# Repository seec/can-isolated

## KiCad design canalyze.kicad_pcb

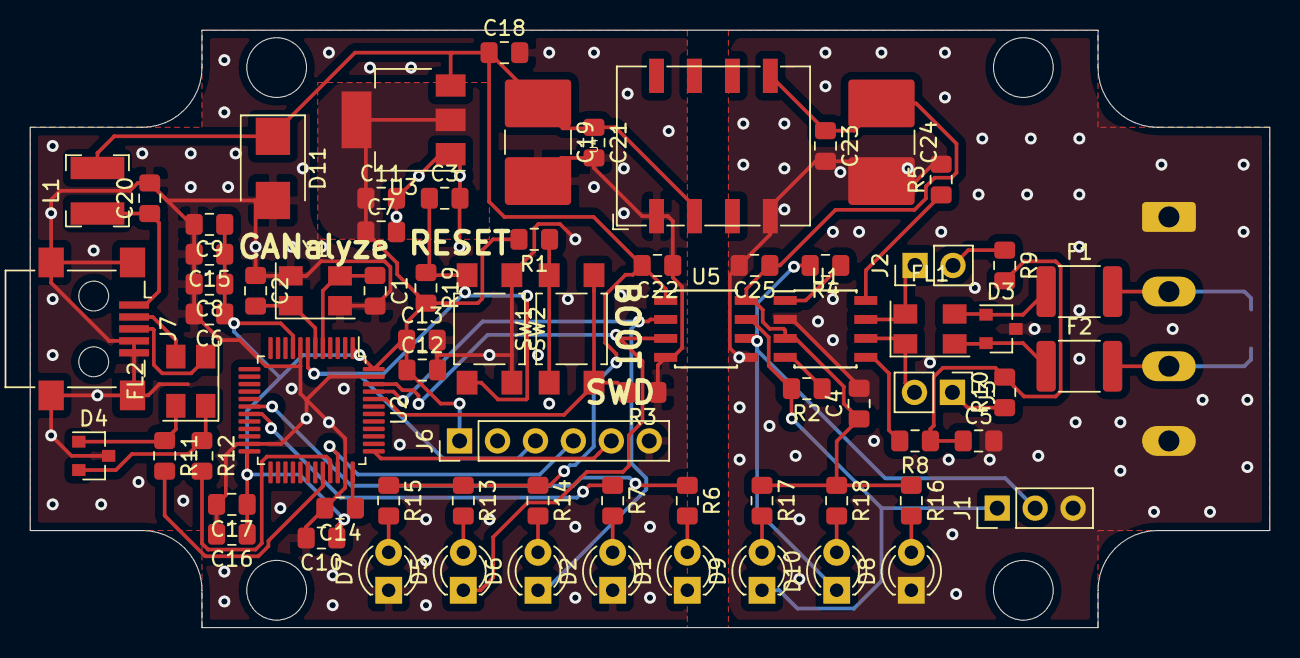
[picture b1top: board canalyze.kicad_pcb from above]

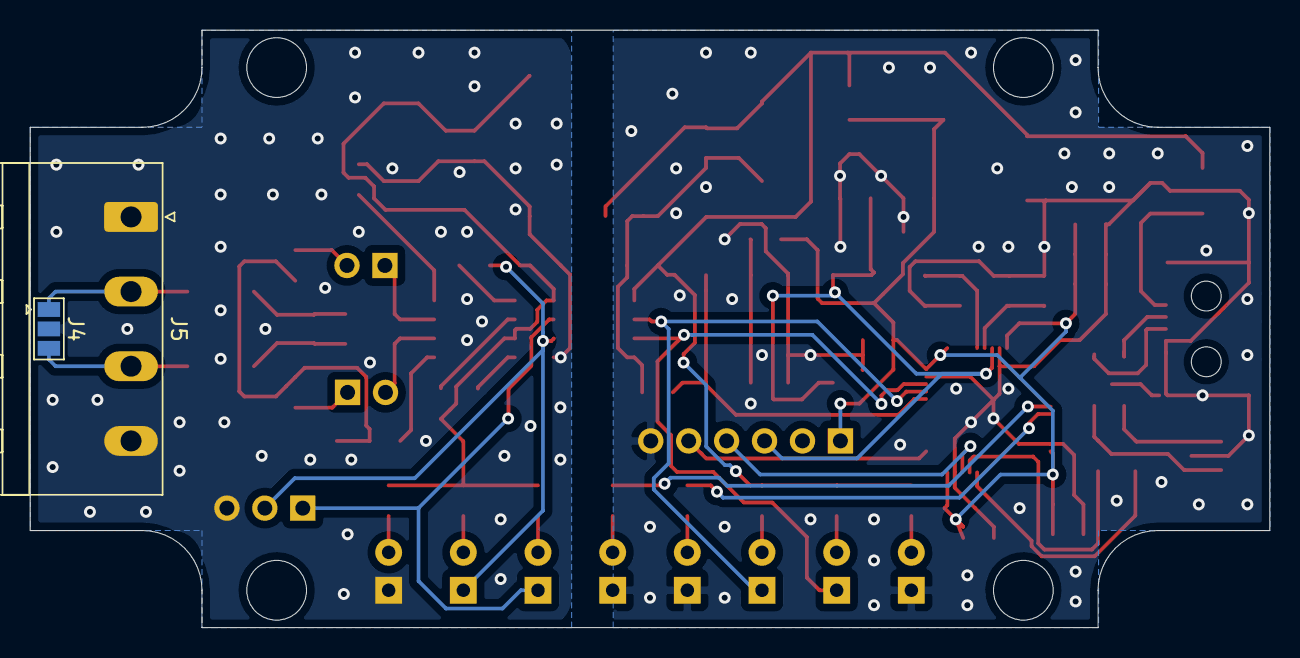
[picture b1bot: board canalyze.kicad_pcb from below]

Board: 2 copper layers, 83.0 x 40.0 mm, 75 parts (2 on the bottom side), 46 nets.

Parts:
C1, C2: 15p; C_0805_2012Metric_Pad1.15x1.40mm_HandSolder
C3, C6, C8, C9, C11, C12, C13: 0.1u; C_0805_2012Metric_Pad1.15x1.40mm_HandSolder
C4, C22, C25: 0.1U; C_0805_2012Metric_Pad1.15x1.40mm_HandSolder
C5: 10n; C_0805_2012Metric_Pad1.15x1.40mm_HandSolder
C7, C10, C14: 4.7u; C_0805_2012Metric_Pad1.15x1.40mm_HandSolder
C15: 0.01u; C_0805_2012Metric_Pad1.15x1.40mm_HandSolder
C16: 1u; C_0805_2012Metric_Pad1.15x1.40mm_HandSolder
C17, C18: 1U; C_0805_2012Metric_Pad1.15x1.40mm_HandSolder
C19, C24: CP; C_2816_7142Metric_Pad3.20x4.45mm_HandSolder
C20: 0.01U; C_0805_2012Metric_Pad1.15x1.40mm_HandSolder
C21, C23: C; C_0805_2012Metric_Pad1.15x1.40mm_HandSolder
D1: LED_GREEN; LED_D3.0mm
D2: LED_RED; LED_D3.0mm
D3, D4: PESD2CAN; SOT-23
D5, D6, D7, D8, D9, D10: LED; LED_D3.0mm
D11: 1.5KE6.5A; D_SMB
F1, F2: Polyfuse; Fuse_1812_4532Metric_Pad1.30x3.40mm_HandSolder
FL1, FL2: EMI_Filter_LL; Crystal_SMD_5032-4Pin_5.0x3.2mm
J1: Conn_01x03; PinHeader_1x03_P2.54mm_Vertical
J2, J3: Conn_01x02_Male; PinHeader_1x02_P2.54mm_Vertical
J4: GS3; SolderJumper-3_P1.3mm_Open_Pad1.0x1.5mm
J5: Conn_01x04_Male; PhoenixContact_MSTBA_2,5_4-G_1x04_P5.00mm_Horizontal
J6: Conn_01x06; PinHeader_1x06_P2.54mm_Vertical
J7: USB_B; USB_Mini-B_Lumberg_2486_01_Horizontal
L1: Ferrite_Bead; L_Bourns-SRN4018
R1: 510; R_0805_2012Metric_Pad1.15x1.40mm_HandSolder
R2, R4, R8: 300R; R_0805_2012Metric_Pad1.15x1.40mm_HandSolder
R3: 10k; R_0805_2012Metric_Pad1.15x1.40mm_HandSolder
R5: 2.2K; R_0805_2012Metric_Pad1.15x1.40mm_HandSolder
R6, R7: 120; R_0805_2012Metric_Pad1.15x1.40mm_HandSolder
R9, R10: 60R; R_0805_2012Metric_Pad1.15x1.40mm_HandSolder
R11, R12: 100R; R_0805_2012Metric_Pad1.15x1.40mm_HandSolder
R13, R14, R15, R16, R17, R18: 1K; R_0805_2012Metric_Pad1.15x1.40mm_HandSolder
R19: 100k; R_0805_2012Metric_Pad1.15x1.40mm_HandSolder
SW1, SW2: SW_PUSH; SW_SPST_TL3305A
U1: MCP2561-H/SN; SOIC-8_3.9x4.9mm_P1.27mm
U2: STM32F042C6Tx; LQFP-48_7x7mm_P0.5mm
U3: NCP1117-3.3_SOT223; SOT-223-3_TabPin2
U4: AM1L-N-Z
U5: ISO7321C; SOIC-8_3.9x4.9mm_P1.27mm
Y1: 16M; Crystal_SMD_5032-4Pin_5.0x3.2mm

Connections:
+3V3: C6.1, C7.1, C8.1, C9.1, C10.1, C11.1, C12.1, C13.1, C14.1, C15.1, C16.1, C17.1, J6.1, R1.2, R19.2, U2.1, U2.9, U2.24, U2.36, U2.48, U3.2
+5V: C18.1, C19.1, C21.1, C22.2, D11.1, L1.1, R13.1, R14.1, R15.1, U3.3, U4.2, U5.1
+5V1: C4.1, C23.1, C24.1, C25.1, R16.1, R17.1, R18.1, U1.3, U4.5, U5.8
/H: F1.2, J4.1, J5.2
/L: F2.2, J4.3, J5.3
CAN_RX: D6.1, U2.45, U5.2
CAN_TX: D5.1, U2.46, U5.3
GND: C1.2, C2.1, C3.2, C6.2, C7.2, C8.2, C9.2, C10.2, C11.2, C12.2, C13.2, C14.2, C15.2, C16.2, C17.2, C18.2, C19.2, C20.2, C21.2, C22.1, D1.1, D2.1, D4.3, D7.1, D11.2, J6.6, J7.4, J7.5, R3.1, SW2.1, U2.8, U2.23, U2.35, U2.47, U3.1, U4.1, U5.4, Y1.2, Y1.4
GNDPWR: C4.2, C5.2, C23.2, C24.2, C25.2, D3.3, D8.1, J1.3, J4.2, J5.1, J5.4, R5.2, U1.2, U4.4, U5.5
IsoCAN_RX: D9.1, J1.1, R2.2, U5.7
IsoCAN_TX: D10.1, J1.2, R4.2, U5.6
NRST: C3.1, J6.3, R19.1, SW2.2, U2.7
unnamed: C1.1, U2.5, Y1.3
unnamed: C2.2, U2.6, Y1.1
unnamed: C5.1, R8.1, R9.2, R10.2
unnamed: C20.1, J7.1, L1.2
unnamed: D1.2, R6.2
unnamed: D2.2, R7.2
unnamed: D3.1, F1.1, FL1.3
unnamed: D3.2, F2.1, FL1.2
unnamed: D4.1, FL2.4, R11.1
unnamed: D4.2, FL2.1, R12.1
unnamed: D5.2, R13.2
unnamed: D6.2, R14.2
unnamed: D7.2, R15.2
unnamed: D8.2, R16.2
unnamed: D9.2, R17.2
unnamed: D10.2, R18.2
unnamed: FL1.1, J3.2, U1.6
unnamed: FL1.4, J2.1, U1.7
unnamed: FL2.2, J7.3
unnamed: FL2.3, J7.2
unnamed: J2.2, R9.1
unnamed: J3.1, R10.1
unnamed: R1.1, SW1.1
unnamed: R2.1, U1.4
unnamed: R3.2, SW1.2, U2.44
unnamed: R4.1, U1.1
unnamed: R5.1, U1.8
unnamed: R6.1, U2.18
unnamed: R7.1, U2.19
unnamed: R8.2, U1.5
unnamed: R11.2, U2.32
unnamed: R12.2, U2.33
SWCLK: J6.5, U2.37
SWDIO: J6.4, U2.34
